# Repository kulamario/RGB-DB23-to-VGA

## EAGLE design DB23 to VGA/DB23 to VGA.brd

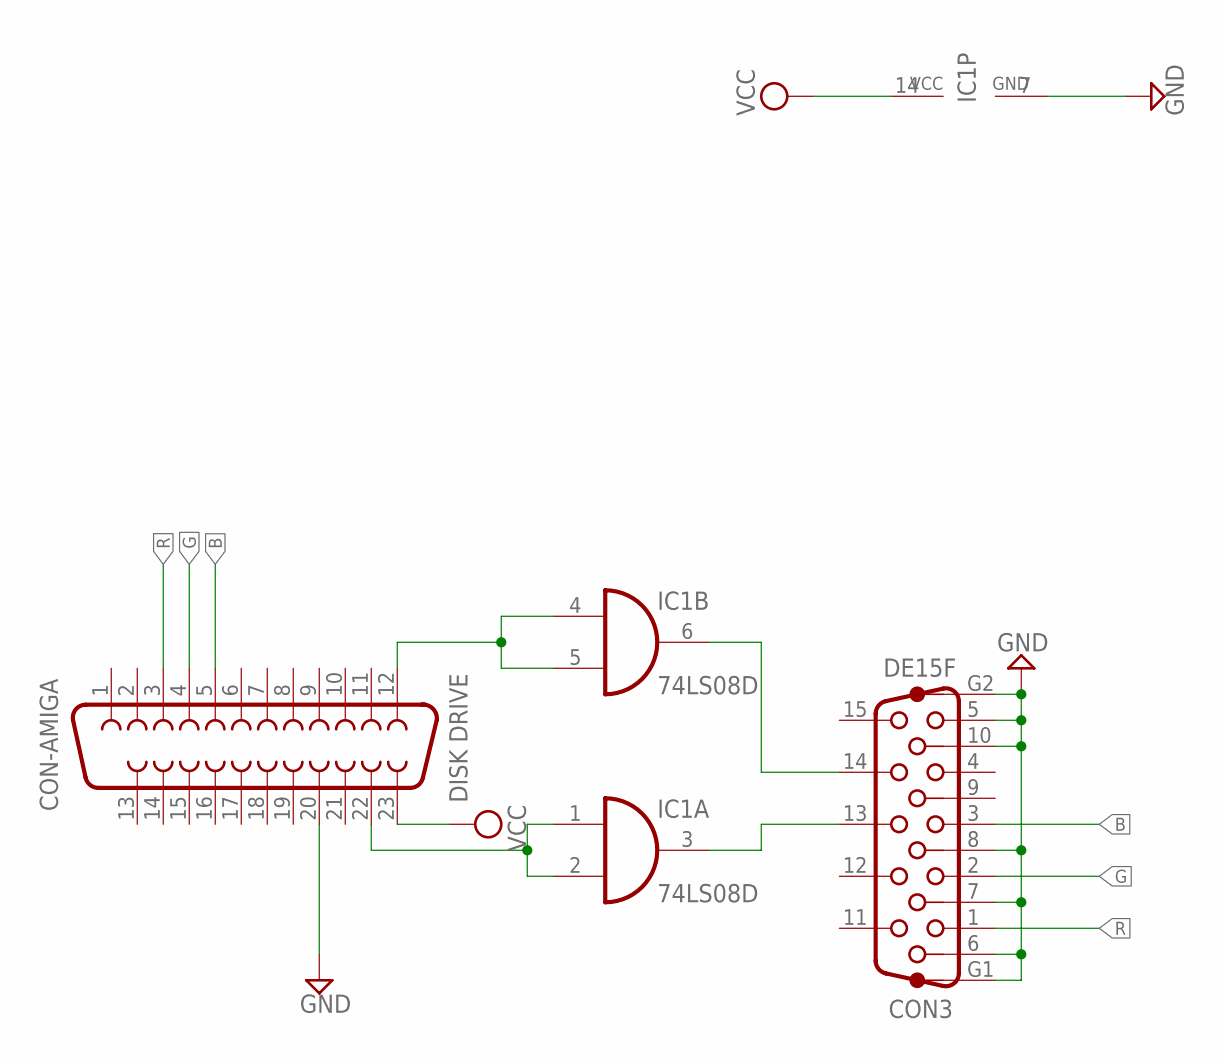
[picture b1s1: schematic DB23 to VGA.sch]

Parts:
CON3: DE15F; VGA-FHP
CON-AMIGA: DISK DRIVE; DB23
IC1: 74LS08D; SO14

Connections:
B: CON3.3, CON-AMIGA.5
G: CON3.2, CON-AMIGA.4
GND: CON3.5, CON3.6, CON3.7, CON3.8, CON3.10, CON3.G1, CON3.G2, CON-AMIGA.20, IC1.7 (GND)
unnamed: CON3.13, IC1.3 (O)
unnamed: CON-AMIGA.12, IC1.4 (I0), IC1.5 (I1)
unnamed: CON3.14, IC1.6 (O)
unnamed: CON-AMIGA.22, IC1.1 (I0), IC1.2 (I1)
R: CON3.1, CON-AMIGA.3
VCC: CON-AMIGA.23, IC1.14 (VCC)

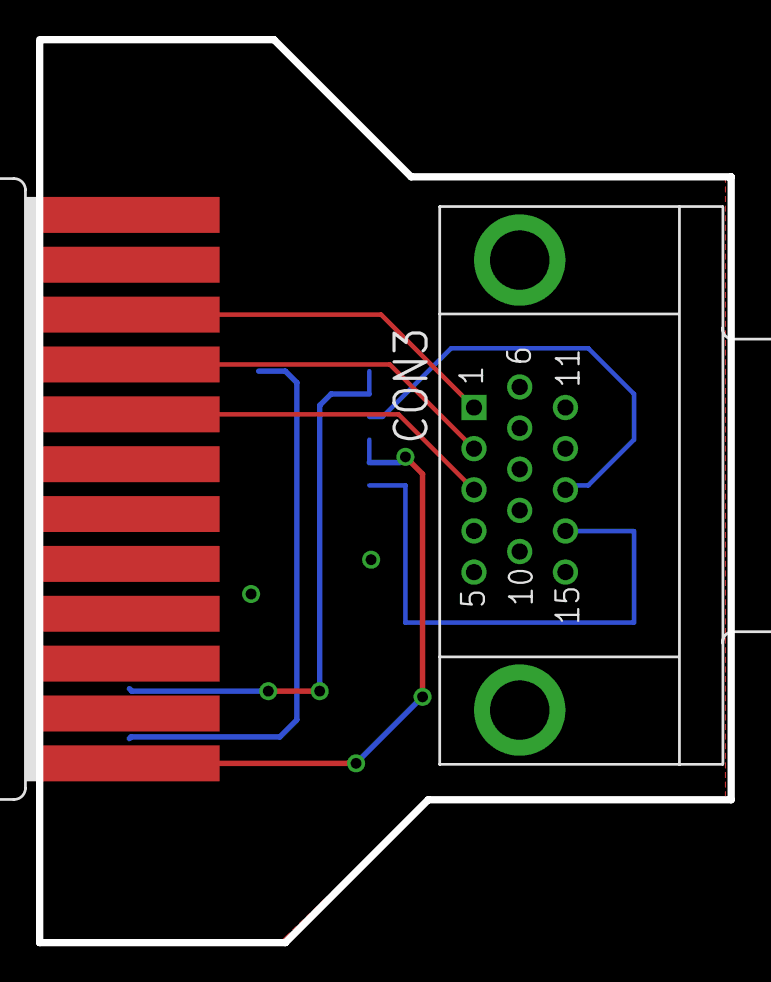
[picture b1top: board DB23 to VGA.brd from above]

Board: 2 copper layers, 38.4 x 50.2 mm, 3 parts (1 on the bottom side), 9 nets.
